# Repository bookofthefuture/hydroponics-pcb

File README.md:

# hydroponics-pcb

KiCad PCB designs for the hydroponics monitoring/control system on a two-tier
IKEA growing rack.

## Boards

| Board | Status | MCU | Purpose |
|-------|--------|-----|---------|
| `tray-board` | fab-ready: ERC/DRC/schematic-parity clean, routed with GND pours + stitching, full JLC BOM (all Basic parts) / CPL / gerbers generated | socketed ESP32 30-pin DevKit | Per-tray sensor + display node. One per tray (top / bottom). |
| `reservoir-board` | not started | ESP32 (TBD) | Reservoir-side control: fill pumps, A/B + pH dosing pumps, level/EC/pH/temp sensing. |

Grow-lamp switching currently stays on the original ESP8266 `hydroponics_monitor`
node and is out of scope for these boards (may move to the reservoir board later).

## Tray board peripherals

| Function | Part | Bus | Notes |
|----------|------|-----|-------|
| ToF distance (water level) | VL53L0X / VL53L1X | I²C 3.3 V | Shared SDA/SCL |
| Air pressure (+ humidity/temp on BME) | BMP280 / BME280 | I²C 3.3 V | Shared SDA/SCL |
| Lux level | BH1750 | I²C 3.3 V | Shared SDA/SCL |
| Water temperature | DS18B20 | 1-Wire 3.3 V | Dedicated GPIO, 4.7 kΩ pull-up |
| Display | 2.4" 240×320 (ILI9341 *or* ST7789V - see below), resistive touch (XPT2046) + SD card | SPI (shared bus, separate CS lines) | LVGL touch UI; SD card wired but not yet used by firmware |

Display connector (J2, 14-pin) pinout: VCC, GND, CS(D5), RESET(D4), DC(D2),
MOSI(D23), SCK(D18), LED(D15), MISO(D34), T_CLK(D18, shared), T_CS(D14),
T_DIN(D23, shared), T_DO(D34, shared), T_IRQ(D35). SD card connector (J3,
4-pin, separate from J2): CS(D19), MOSI(D23, shared), MISO(D34, shared),
SCK(D18, shared). New GPIOs used: 14, 19, 34, 35 — none of these were
previously assigned, so add them to the ESPHome configs without touching the
existing pin numbers.

**Display controller chip varies by batch**: the module is sold as
"LCD Wiki MSP2401/MSP2402", mechanically confirmed to match the footprint
here (see `docs/TODO.md`), but LCDWiki has shipped different driver silicon
under that same model number. The tray-board bench-test unit (2026-09-14)
turned out to be ST7789V, not the documented ILI9341 — sending
ILI9341-specific init commands (extended power/gamma registers) to it left
the panel half-configured (visible as vertical RGB banding), and the bug
turned out to be twofold: wrong driver *and* a bad display unit, only found
once the driver was corrected. **Don't assume the chip from the box label —
check the panel actually responds correctly to its documented driver before
troubleshooting anything else** (wiring, buffer size, rotation, etc.) on a
new module from this line. See the live ESPHome config in the `ha-config`
repo (`esphome/hydro-tray-ui.yaml`) for the working ST7789V setup.

No high-power switching on the tray board. An SP3485EN RS-485 transceiver
(120 Ω termination, direction pin on GPIO12) links the two tray boards to the
reservoir board.

## Comms

All three ESPs talk to Home Assistant over WiFi (ESPHome native API). The tray
boards *also* talk to the reservoir board over RS-485 — a local wired link so
fill-level reads and pump control don't depend on WiFi/HA. The reservoir is the
controlling node.

## Firmware

ESPHome configs live in the separate `ha-config` repo under `esphome/`
(`hydro-top-tray.yaml`, `hydro-bottom-tray.yaml`). The pin map is shared between
the schematic here and those configs — keep them in sync.

## Repo layout

```
tray-board/        KiCad project for the tray sensor board
reservoir-board/   (future) KiCad project for the reservoir board
shared-library/    custom symbol (New_Library) + footprint (Library.pretty)
                   library, referenced by both boards' sym-lib-table/
                   fp-lib-table via ${KIPRJMOD}/../../shared-library/ - keep
                   custom parts (ESP32 DevKit socket, display modules, etc.)
                   here rather than per-board copies, which drift silently
docs/              pin maps, block diagrams, datasheets
```

## Working with KiCad from the CLI

Requires KiCad 10.x (`kicad-cli`) plus the standard symbol/footprint libraries.

```
tools/fab.sh tray-board
```

runs ERC + DRC (fails on any error/warning) and writes a JLCPCB-ready set to
`tray-board/production/` (git-ignored — regenerated from source): gerbers
(Protel extensions) + separate PTH/NPTH Excellon drill files, zipped as
`<name>-gerbers.zip`; `<name>-cpl.csv` (SMD-only pick-and-place, DNP parts
excluded); `<name>-bom.csv` (DNP excluded, `LCSC Part #` column from each
part's `LCSC` schematic field). Parts you're sourcing/fitting yourself (e.g.
the socketed ESP32 module) should be marked Do Not Populate in the schematic
so they're left out of both the BOM and the CPL automatically.

It also runs `tools/check_pins.py`, which checks the MCU's pin usage for
hardware hazards ERC doesn't catch — currently ESP32 strapping pins (GPIO0,
2, 5, 12, 15) with an external pull that conflicts with their required
boot-time level, GPIO6-11 (internal flash, must never be used externally),
and UART0 (GPIO1/3, reserved for USB-serial). Fails the build on any
ERROR-severity finding; can also be run standalone:

```
tools/check_pins.py path/to/board.kicad_sch
```

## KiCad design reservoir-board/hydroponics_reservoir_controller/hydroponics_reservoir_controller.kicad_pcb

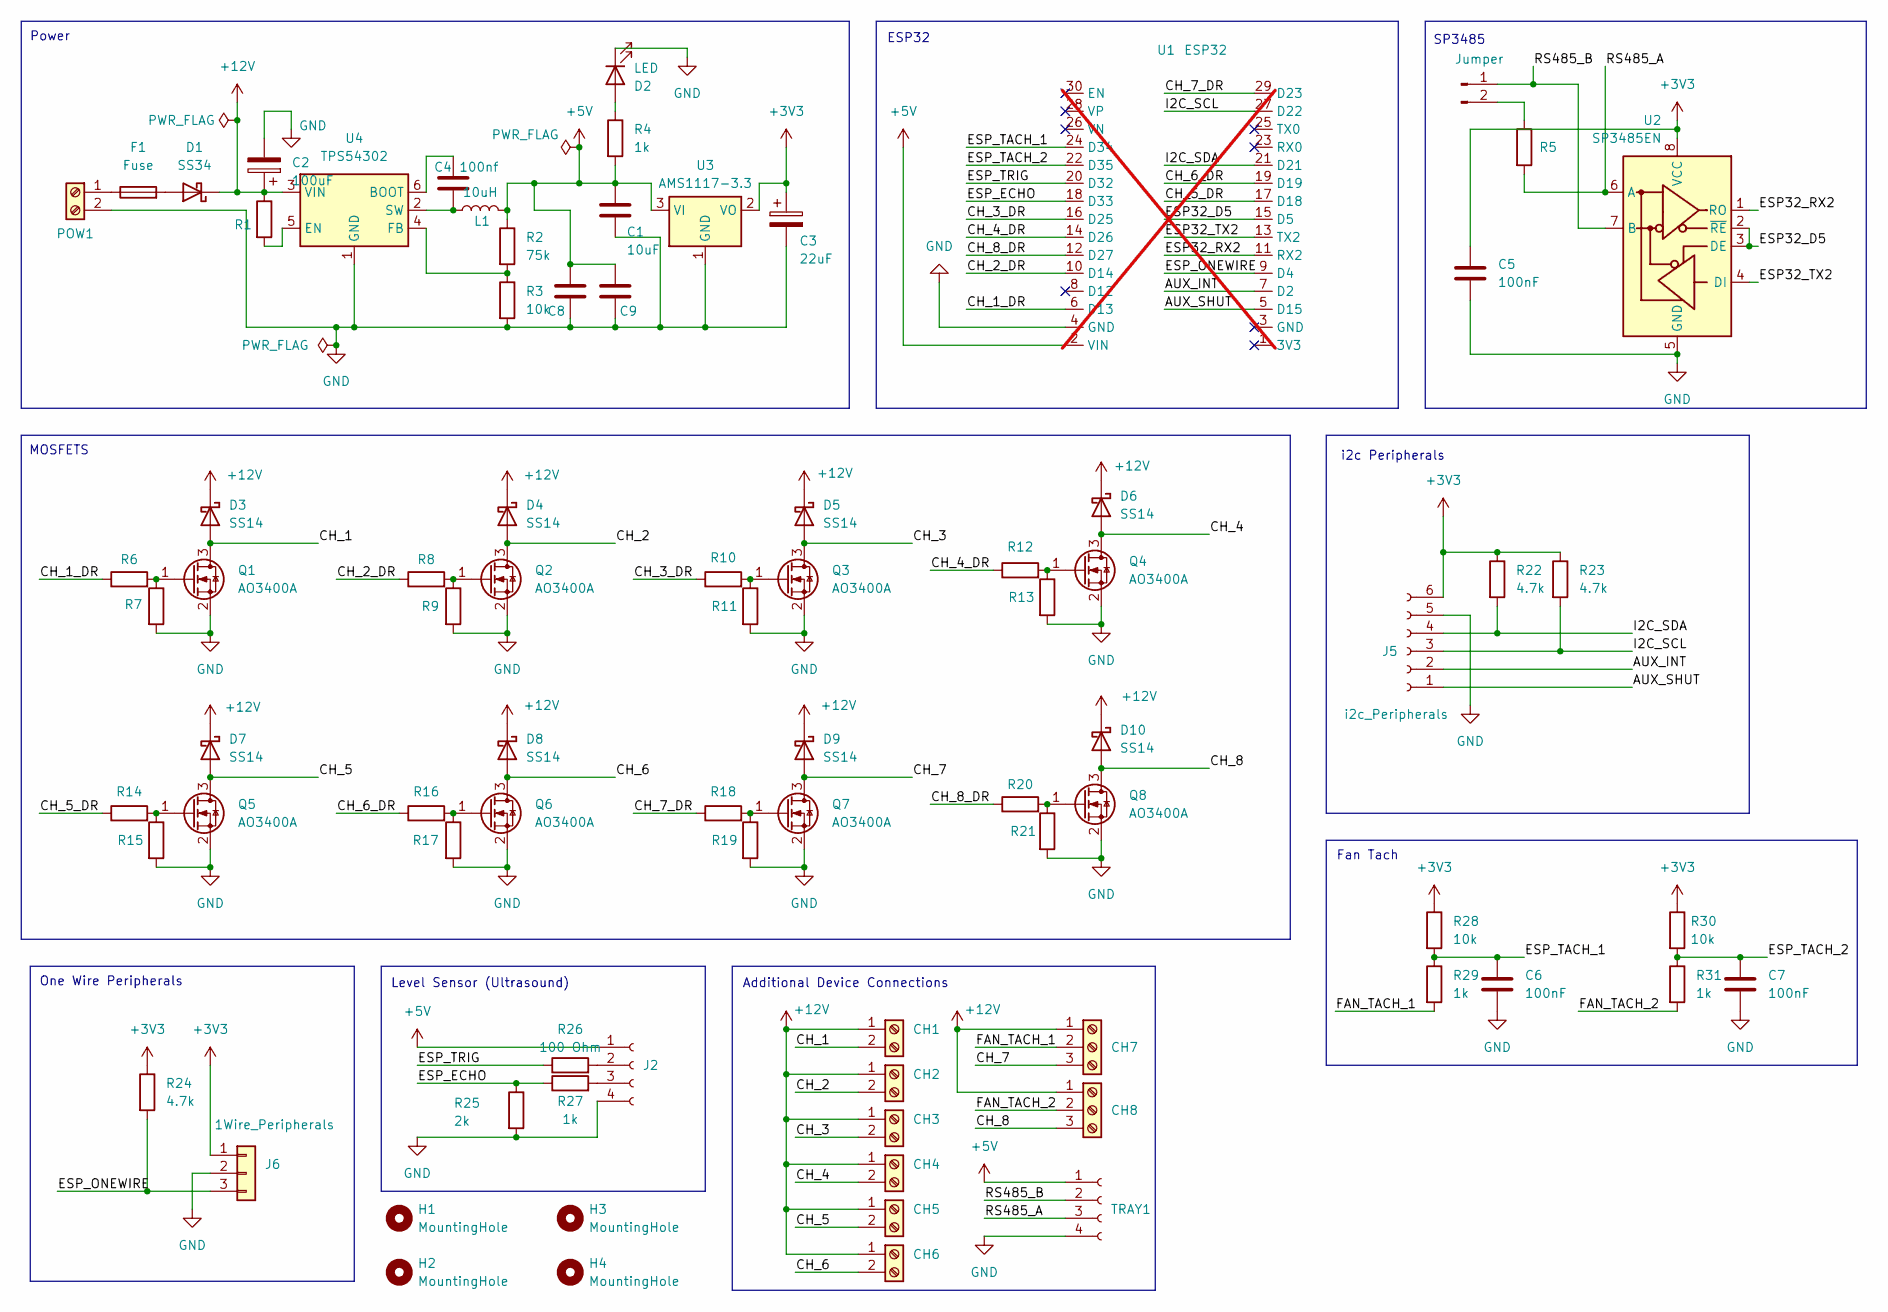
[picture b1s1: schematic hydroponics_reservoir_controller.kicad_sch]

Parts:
C1: 10uF; C_1206_3216Metric; LCSC C13585
C2: 100uF; CP_Elec_6.3x7.7; LCSC C970685
C3: 22uF; CP_EIA-3528-21_Kemet-B; LCSC C24518
C4: 100nf; C_1206_3216Metric; LCSC C24497
C5, C6, C7: 100nF; C_0805_2012Metric; LCSC C49678
C8, C9: 22uF; C_1206_3216Metric; LCSC C338055
CH1, CH2, CH3, CH4, CH5, CH6: Screw_Terminal_01x02; TerminalBlock_Phoenix_PT-1,5-2-3.5-H_1x02_P3.50mm_Horizontal; LCSC C474892
CH7, CH8: Screw_Terminal_01x03; TerminalBlock_Phoenix_PT-1,5-3-3.5-H_1x03_P3.50mm_Horizontal; LCSC C474893
D1: SS34; D_SMA; LCSC C8678
D2: LED; LED_0805_2012Metric; LCSC C2297
D3, D4, D5, D6, D7, D8, D9, D10: SS14; D_SMA; LCSC C2480
F1: Fuse; Fuse_2920_7451Metric; LCSC C207091
H1, H2, H3, H4: MountingHole; MountingHole_3.2mm_M3_Pad
J1: Jumper; PinHeader_1x02_P2.54mm_Vertical; LCSC C36717
J2: Conn_01x04_Socket; JST_XH_B4B-XH-A_1x04_P2.50mm_Vertical; LCSC C144395
J5: i2c_Peripherals; JST_XH_B6B-XH-A_1x06_P2.50mm_Vertical; LCSC C144397
J6: 1Wire_Peripherals; JST_XH_B3B-XH-A_1x03_P2.50mm_Vertical; LCSC C144394
L1: 10uH; L_Bourns_SRP6060FA; LCSC C2046759
POW1: Screw_Terminal_01x02; TerminalBlock_Phoenix_PT-1,5-2-5.0-H_1x02_P5.00mm_Horizontal; LCSC C474881
Q1, Q2, Q3, Q4, Q5, Q6, Q7, Q8: AO3400A; SOT-23; LCSC C20917
R1: 100k; R_0805_2012Metric; LCSC C149504
R2: 75k; R_0805_2012Metric; LCSC C17819
R3, R7, R9, R11, R13, R15, R17, R19, R21, R28, R30: 10k; R_0805_2012Metric; LCSC C17414
R4, R27, R29, R31: 1k; R_0805_2012Metric; LCSC C17513
R5: 120 Ohm; R_0805_2012Metric; LCSC C17437
R6, R8, R10, R12, R14, R16, R18, R20, R26: 100 Ohm; R_0805_2012Metric; LCSC C17408
R22, R23, R24: 4.7k; R_0805_2012Metric; LCSC C17673
R25: 2k; R_0805_2012Metric; LCSC C17604
TRAY1: Conn_01x04_Socket; JST_XH_B4B-XH-A_1x04_P2.50mm_Vertical; LCSC C144395
U1: ESP32; ESP32_DevKit_30Pin; not fitted
U2: SP3485EN; SOIC-8_3.9x4.9mm_P1.27mm; LCSC C8963
U3: AMS1117-3.3; SOT-223-3_TabPin2; LCSC C6186
U4: TPS54302; SOT-23-6; LCSC C311983

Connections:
+3V3: C3.1, C5.1, J5.6, J6.1, R22.1, R23.1, R24.1, R28.1, R30.1, U2.8 (VCC), U3.2 (VO); also elsewhere on the board
+5V: C1.1, C8.1, C9.1, J2.1, L1.2, R2.1, R4.2, TRAY1.1, U1.2 (VIN), U3.3 (VI); also elsewhere on the board
/AUX_INT: J5.2, U1.7 (D2); also elsewhere on the board
/AUX_SHUT: J5.1, U1.5 (D15); also elsewhere on the board
/CH_1: CH1.2, D3.2 (A), Q1.3 (D)
/CH_1_DR: R6.1, U1.6 (D13)
/CH_2: CH2.2, D4.2 (A), Q2.3 (D)
/CH_2_DR: R8.1, U1.10 (D14)
/CH_3: CH3.2, D5.2 (A), Q3.3 (D)
/CH_3_DR: R10.1, U1.16 (D25)
/CH_4: CH4.2, D6.2 (A), Q4.3 (D)
/CH_4_DR: R12.1, U1.14 (D26)
/CH_5: CH5.2, D7.2 (A), Q5.3 (D)
/CH_5_DR: R14.1, U1.17 (D18)
/CH_6: CH6.2, D8.2 (A), Q6.3 (D)
/CH_6_DR: R16.1, U1.19 (D19)
/CH_7: CH7.3, D9.2 (A), Q7.3 (D)
/CH_7_DR: R18.1, U1.29 (D23)
/CH_8: CH8.3, D10.2 (A), Q8.3 (D)
/CH_8_DR: R20.1, U1.12 (D27)
/ESP32_D5: U1.15 (D5), U2.2 (~RE), U2.3 (DE)
/ESP32_RX2: U1.11 (RX2), U2.1 (RO)
/ESP32_TX2: U1.13 (TX2), U2.4 (DI)
/ESP_ECHO: R25.1, R27.1, U1.18 (D33)
/ESP_ONEWIRE: J6.3, R24.2, U1.9 (D4); also elsewhere on the board
/ESP_TACH_1: C6.1, R28.2, R29.1, U1.24 (D34)
/ESP_TACH_2: C7.1, R30.2, R31.1, U1.22 (D35)
/ESP_TRIG: R26.1, U1.20 (D32)
/FAN_TACH_1: CH7.2, R29.2
/FAN_TACH_2: CH8.2, R31.2
/I2C_SCL: J5.3, R23.2, U1.27 (D22); also elsewhere on the board
/I2C_SDA: J5.4, R22.2, U1.21 (D21); also elsewhere on the board
/RS485_A: R5.2, TRAY1.3, U2.6 (A); also elsewhere on the board
/RS485_B: J1.1, TRAY1.2, U2.7 (B); also elsewhere on the board
GND: C1.2, C2.2, C3.2, C5.2, C6.2, C7.2, C8.2, C9.2, D2.1 (K), J2.4, J5.5, J6.2, POW1.2, Q1.2 (S), Q2.2 (S), Q3.2 (S), Q4.2 (S), Q5.2 (S), Q6.2 (S), Q7.2 (S), Q8.2 (S), R3.2, R7.2, R9.2, R11.2, R13.2, R15.2, R17.2, R19.2, R21.2, R25.2, TRAY1.4, U1.4 (GND), U2.5 (GND), U3.1 (GND), U4.1 (GND); also elsewhere on the board
unnamed: D1.2 (A), F1.2
unnamed: D2.2 (A), R4.1
unnamed: J1.2, R5.1
unnamed 38: J2.2, R26.2; also elsewhere on the board
unnamed 39: J2.3, R27.2; also elsewhere on the board
unnamed: Q1.1 (G), R6.2, R7.1
unnamed: Q2.1 (G), R8.2, R9.1
unnamed: Q3.1 (G), R10.2, R11.1
unnamed: Q4.1 (G), R12.2, R13.1
unnamed: Q5.1 (G), R14.2, R15.1
unnamed: Q6.1 (G), R16.2, R17.1
unnamed: Q7.1 (G), R18.2, R19.1
unnamed: Q8.1 (G), R20.2, R21.1
unnamed: C4.1, U4.6 (BOOT)
unnamed: R1.2, U4.5 (EN)
unnamed: R2.2, R3.1, U4.4 (FB)
unnamed: C4.2, L1.1, U4.2 (SW)

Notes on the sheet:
One Wire Peripherals
Additional Device Connections
SP3485
ESP32
MOSFETS
Level Sensor (Ultrasound)
Fan Tach
i2c Peripherals
Power

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
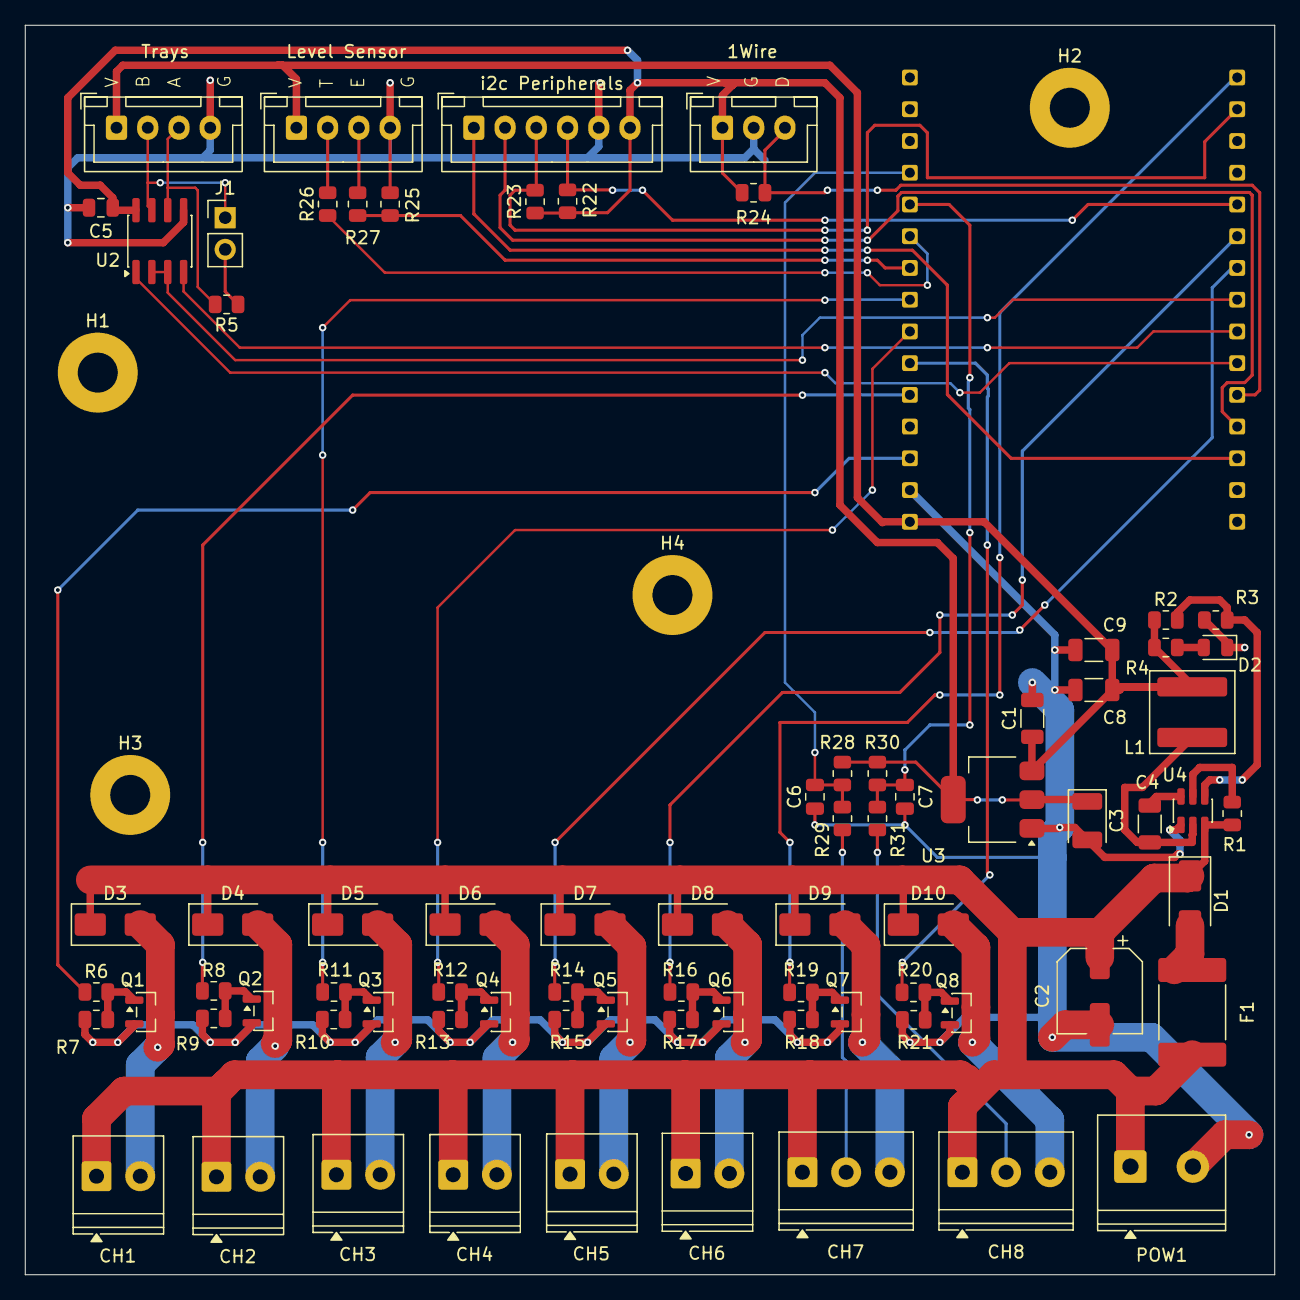
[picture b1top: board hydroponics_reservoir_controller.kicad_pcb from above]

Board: 2 copper layers, 100.0 x 100.0 mm, 82 parts (0 on the bottom side), 53 nets.

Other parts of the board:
1Wire: 1Wire_Peripherals; JST_XH_B3B-XH-A_1x03_P2.50mm_Vertical
Level Sensor: Conn_01x04_Socket; JST_XH_B4B-XH-A_1x04_P2.50mm_Vertical
Trays: Conn_01x04_Socket; JST_XH_B4B-XH-A_1x04_P2.50mm_Vertical
i2c Peripherals: i2c_Peripherals; JST_XH_B6B-XH-A_1x06_P2.50mm_Vertical

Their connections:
+3V3: 1Wire.1, i2c Peripherals.6; also elsewhere on the board
+5V: Level Sensor.1, Trays.1; also elsewhere on the board
/AUX_INT: i2c Peripherals.2; also elsewhere on the board
/AUX_SHUT: i2c Peripherals.1; also elsewhere on the board
/ESP_ONEWIRE: 1Wire.3; also elsewhere on the board
/I2C_SCL: i2c Peripherals.3; also elsewhere on the board
/I2C_SDA: i2c Peripherals.4; also elsewhere on the board
/RS485_A: Trays.3; also elsewhere on the board
/RS485_B: Trays.2; also elsewhere on the board
GND: 1Wire.2, Level Sensor.4, Trays.4, i2c Peripherals.5; also elsewhere on the board
unnamed 38: Level Sensor.2; also elsewhere on the board
unnamed 39: Level Sensor.3; also elsewhere on the board

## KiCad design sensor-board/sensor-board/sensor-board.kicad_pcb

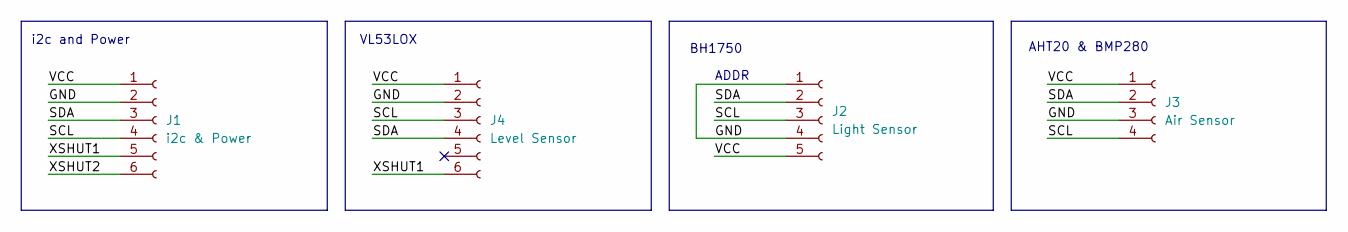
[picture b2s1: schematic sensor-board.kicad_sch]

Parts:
J1: i2c & Power; PinSocket_1x06_P2.54mm_Vertical
J2: Light Sensor; PinSocket_1x05_P2.54mm_Vertical
J3: Air Sensor; PinSocket_1x04_P2.54mm_Vertical
J4: Level Sensor; PinSocket_1x06_P2.54mm_Vertical

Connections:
/GND: J1.2, J2.1, J2.4, J3.3, J4.2
/SCL: J1.4, J2.3, J3.4, J4.3
/SDA: J1.3, J2.2, J3.2, J4.4
/VCC: J1.1, J2.5, J3.1, J4.1
/XSHUT1: J1.5, J4.6
/XSHUT2: J1.6

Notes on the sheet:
BH1750
VL53LOX
i2c and Power
ADDR
AHT20 & BMP280

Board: 2 copper layers, 4 parts (0 on the bottom side), 5 nets, no tracks yet.

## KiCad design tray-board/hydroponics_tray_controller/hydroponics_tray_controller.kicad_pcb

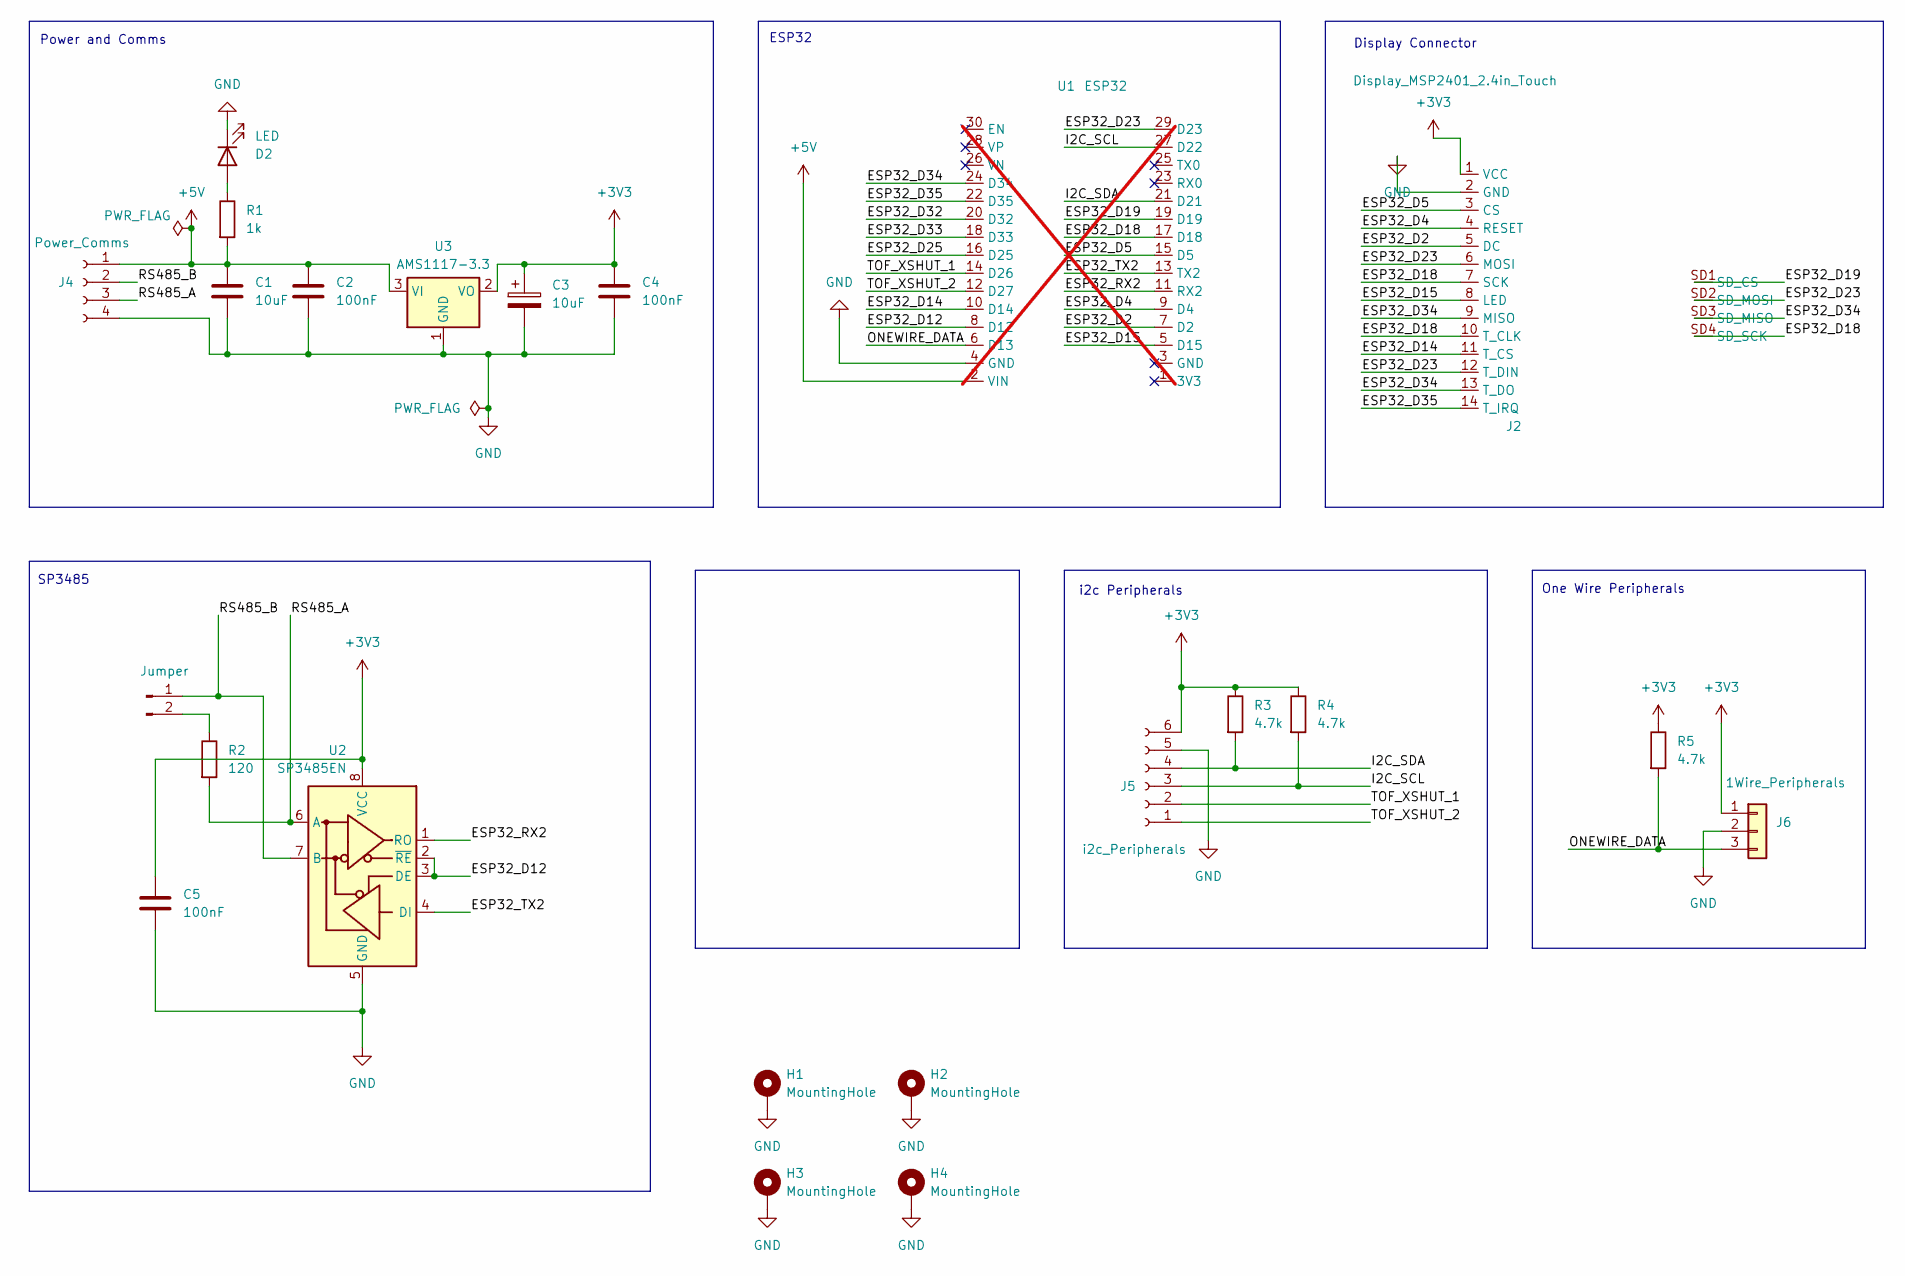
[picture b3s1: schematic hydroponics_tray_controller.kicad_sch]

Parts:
C1: 10uF; C_1206_3216Metric; LCSC C13585
C2, C4, C5: 100nF; C_0805_2012Metric; LCSC C49678
C3: 10uF; C_0805_2012Metric; LCSC C15850
D2: LED; LED_0805_2012Metric; LCSC C2297
H1, H2, H3, H4: MountingHole; MountingHole_3.2mm_M3_Pad_Via
J1: Jumper; PinHeader_1x02_P2.54mm_Vertical
J2: Display_MSP2401_2.4in_Touch
J4: Power_Comms; JST_XH_B4B-XH-A_1x04_P2.50mm_Vertical
J5: i2c_Peripherals; JST_XH_B6B-XH-A_1x06_P2.50mm_Vertical
J6: 1Wire_Peripherals; JST_XH_B3B-XH-A_1x03_P2.50mm_Vertical
R1: 1k; R_0805_2012Metric; LCSC C17513
R2: 120; R_0805_2012Metric; LCSC C17437
R3, R4, R5: 4.7k; R_0805_2012Metric; LCSC C17673
U1: ESP32; ESP32_DevKit_30Pin; not fitted
U2: SP3485EN; SOIC-8_3.9x4.9mm_P1.27mm; LCSC C8963
U3: AMS1117-3.3; SOT-223-3_TabPin2; LCSC C6186

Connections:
+3V3: C3.1, C4.1, C5.1, J2.1 (VCC), J5.6, J6.1, R3.1, R4.1, R5.1, U2.8 (VCC), U3.2 (VO)
+5V: C1.1, C2.1, J4.1, R1.2, U1.2 (VIN), U3.3 (VI)
/ESP32_D2: J2.5 (DC), U1.7 (D2)
/ESP32_D4: J2.4 (RESET), U1.9 (D4)
/ESP32_D5: J2.3 (CS), U1.15 (D5)
/ESP32_D12: U1.8 (D12), U2.2 (~RE), U2.3 (DE)
/ESP32_D14: J2.11 (T_CS), U1.10 (D14)
/ESP32_D15: J2.8 (LED), U1.5 (D15)
/ESP32_D18: J2.7 (SCK), J2.10 (T_CLK), J2.SD4 (SD_SCK), U1.17 (D18)
/ESP32_D19: J2.SD1 (SD_CS), U1.19 (D19)
/ESP32_D23: J2.6 (MOSI), J2.12 (T_DIN), J2.SD2 (SD_MOSI), U1.29 (D23)
/ESP32_D25: U1.16 (D25)
/ESP32_D32: U1.20 (D32)
/ESP32_D33: U1.18 (D33)
/ESP32_D34: J2.9 (MISO), J2.13 (T_DO), J2.SD3 (SD_MISO), U1.24 (D34)
/ESP32_D35: J2.14 (T_IRQ), U1.22 (D35)
/ESP32_RX2: U1.11 (RX2), U2.1 (RO)
/ESP32_TX2: U1.13 (TX2), U2.4 (DI)
/I2C_SCL: J5.3, R4.2, U1.27 (D22)
/I2C_SDA: J5.4, R3.2, U1.21 (D21)
/ONEWIRE_DATA: J6.3, R5.2, U1.6 (D13)
/RS485_A: J4.3, R2.2, U2.6 (A)
/RS485_B: J1.1, J4.2, U2.7 (B)
/TOF_XSHUT_1: J5.2, U1.14 (D26)
/TOF_XSHUT_2: J5.1, U1.12 (D27)
GND: C1.2, C2.2, C3.2, C4.2, C5.2, D2.1 (K), H1.1 (1_1), H2.1 (1_1), H3.1 (1_1), H4.1 (1_1), J2.2 (GND), J4.4, J5.5, J6.2, U1.4 (GND), U2.5 (GND), U3.1 (GND)
unnamed: D2.2 (A), R1.1
unnamed: J1.2, R2.1

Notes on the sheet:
One Wire Peripherals
SP3485
ESP32
Display Connector
i2c Peripherals
Power and Comms

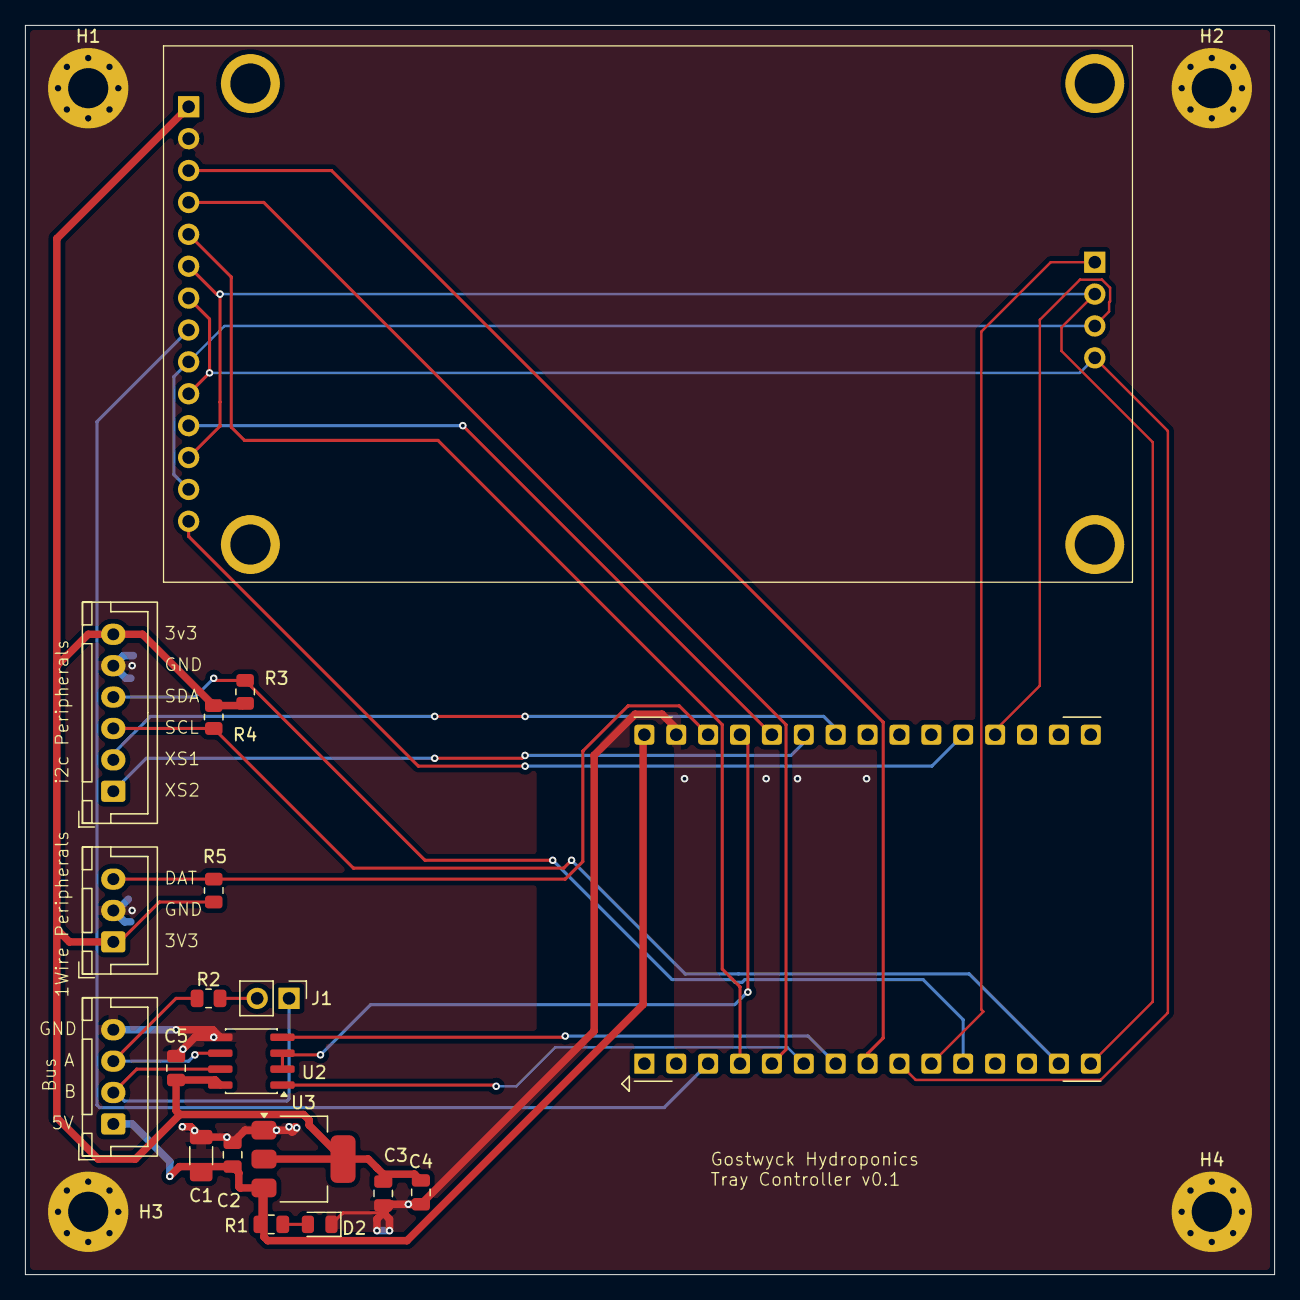
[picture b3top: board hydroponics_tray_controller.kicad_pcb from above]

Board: 2 copper layers, 99.5 x 99.5 mm, 23 parts (0 on the bottom side), 25 nets.
